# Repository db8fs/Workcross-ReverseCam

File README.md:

Workcross-ReverseCam
====================

ESP32-based pcb for providing ESD-safe power supply for a wireless Reverse Camera for an AODES Workcross UTV.

Schematics and PCB are designed using KiCad9.

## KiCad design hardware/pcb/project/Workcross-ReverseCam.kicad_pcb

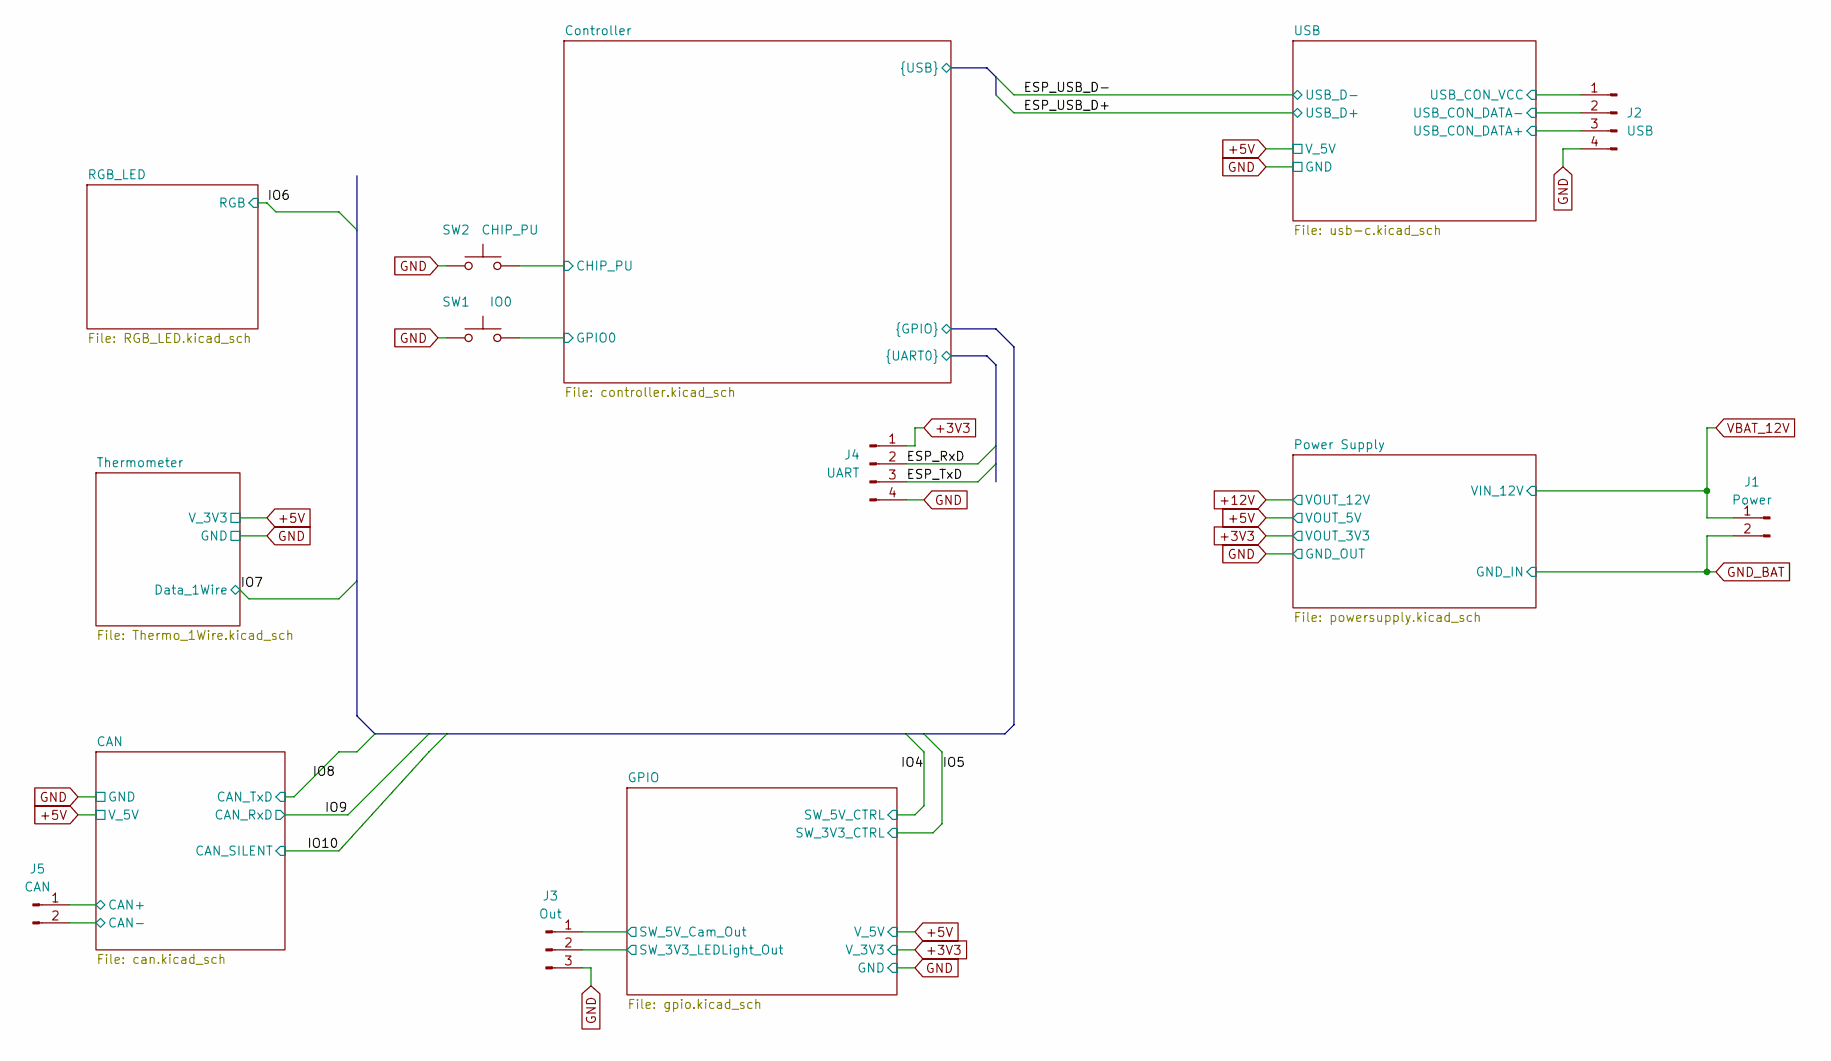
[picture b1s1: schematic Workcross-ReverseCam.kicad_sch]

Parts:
J1: Power; Molex_KK-254_AE-6410-02A_1x02_P2.54mm_Vertical
J2: USB; PinSocket_1x04_P2.54mm_Vertical
J3: Out; PinHeader_1x03_P2.54mm_Horizontal
J4: UART; PinSocket_1x04_P2.54mm_Vertical
J5: CAN; PinSocket_1x02_P2.54mm_Vertical
SW1: IO0; SW_SPST_Omron_B3FS-100xP
SW2: CHIP_PU; SW_SPST_Omron_B3FS-100xP

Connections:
+3V3: J4.1; also elsewhere on the board
/CAN/CAN+: J5.1; also elsewhere on the board
/CAN/CAN-: J5.2; also elsewhere on the board
/Controller/CHIP_PU: SW2.2; also elsewhere on the board
/Controller/ESP.ESP_RxD: J4.2; also elsewhere on the board
/Controller/ESP.ESP_TxD: J4.3; also elsewhere on the board
/Controller/ESP.ESP_USB_D+: J2.3; also elsewhere on the board
/Controller/ESP.ESP_USB_D-: J2.2; also elsewhere on the board
/Controller/GPIO0: SW1.2; also elsewhere on the board
/GPIO/SW_3V3_LEDLight_Out: J3.2; also elsewhere on the board
/GPIO/SW_5V_Cam_Out: J3.1; also elsewhere on the board
/USB/USB_CON_VCC: J2.1; also elsewhere on the board
GND: J2.4, J3.3, J4.4, SW1.1, SW2.1; also elsewhere on the board
GND_BAT: J1.2; also elsewhere on the board
VBAT_12V: J1.1; also elsewhere on the board

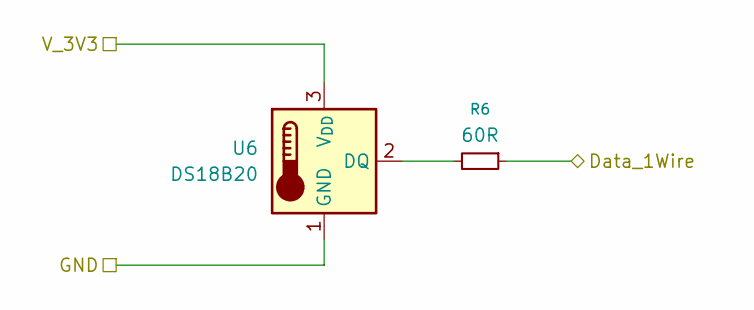
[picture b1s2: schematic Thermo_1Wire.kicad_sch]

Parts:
R6: 60R; R_1206_3216Metric_Pad1.30x1.75mm_HandSolder
U6: DS18B20; TO-92L_HandSolder

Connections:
+5V: U6.3 (V_{DD}); also elsewhere on the board
/Controller/ESP.IO7: R6.1; also elsewhere on the board
GND: U6.1 (GND); also elsewhere on the board
unnamed: R6.2, U6.2 (DQ)

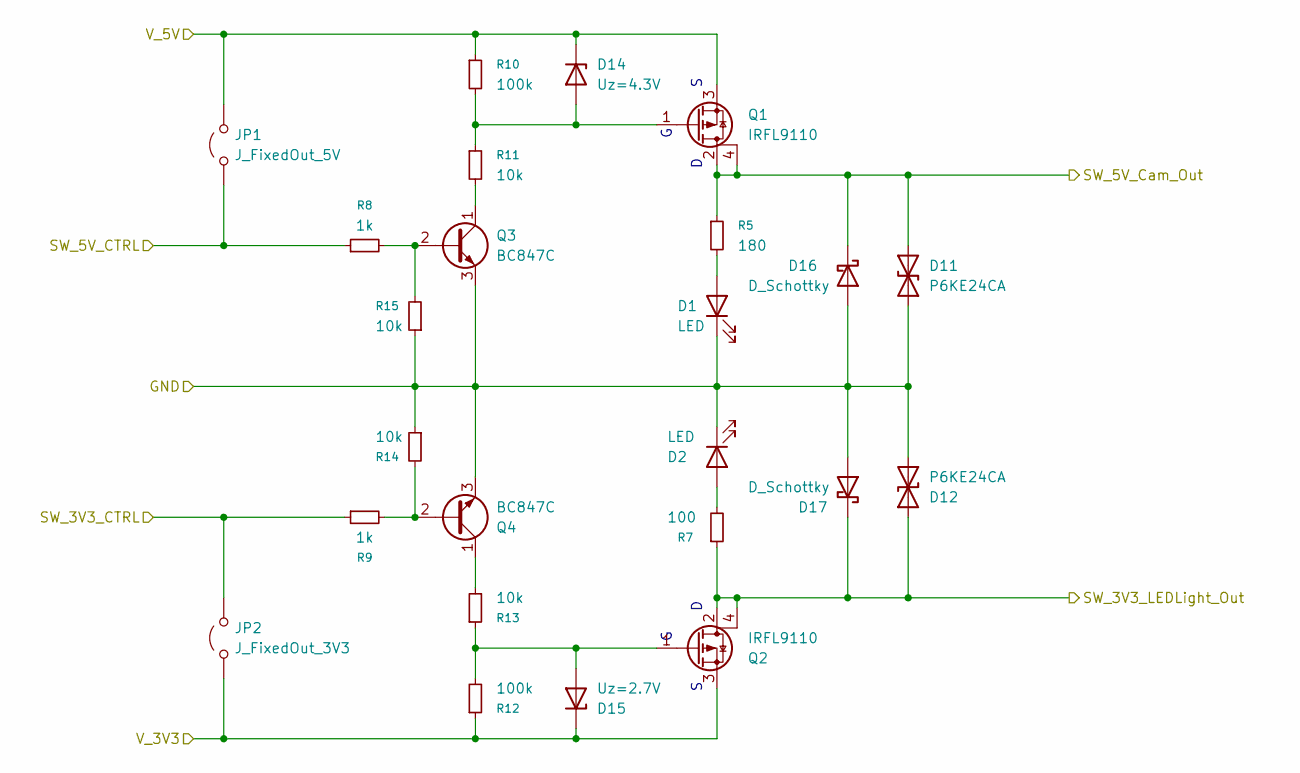
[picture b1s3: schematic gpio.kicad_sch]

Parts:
D1, D2: LED; LED_1206_3216Metric_Pad1.42x1.75mm_HandSolder
D11, D12: P6KE24CA; D_SMB_Handsoldering
D14: Uz=4.3V; D_MiniMELF_Handsoldering
D15: Uz=2.7V; D_MiniMELF_Handsoldering
D16, D17: D_Schottky
JP1: J_FixedOut_5V; TestPoint_2Pads_Pitch2.54mm_Drill0.8mm
JP2: J_FixedOut_3V3; TestPoint_2Pads_Pitch2.54mm_Drill0.8mm
Q1, Q2: IRFL9110; SOT-223-3_TabPin2
Q3, Q4: BC847C; SOT-23
R5: 180; R_1206_3216Metric_Pad1.30x1.75mm_HandSolder
R7: 100; R_1206_3216Metric_Pad1.30x1.75mm_HandSolder
R8, R9: 1k; R_1206_3216Metric_Pad1.30x1.75mm_HandSolder
R10, R12: 100k; R_1206_3216Metric_Pad1.30x1.75mm_HandSolder
R11, R13, R14, R15: 10k; R_1206_3216Metric_Pad1.30x1.75mm_HandSolder

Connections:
+3V3: D15.1 (K), JP2.1 (A), Q2.3 (S), R12.1; also elsewhere on the board
+5V: D14.1 (K), JP1.2 (B), Q1.3 (S), R10.1; also elsewhere on the board
/Controller/ESP.IO4: JP1.1 (A), R8.1; also elsewhere on the board
/Controller/ESP.IO5: JP2.2 (B), R9.1; also elsewhere on the board
/GPIO/SW_3V3_LEDLight_Out: D12.2 (A2), D17.1 (K), Q2.2 (D), Q2.4 (D), R7.1; also elsewhere on the board
/GPIO/SW_5V_Cam_Out: D11.2 (A2), D16.1 (K), Q1.2 (D), Q1.4 (D), R5.1; also elsewhere on the board
GND: D1.1 (K), D2.1 (K), D11.1 (A1), D12.1 (A1), D16.2 (A), D17.2 (A), Q3.3 (E), Q4.3 (E), R14.1, R15.1; also elsewhere on the board
unnamed: D1.2 (A), R5.2
unnamed: D2.2 (A), R7.2
unnamed: D14.2 (A), Q1.1 (G), R10.2, R11.1
unnamed: D15.2 (A), Q2.1 (G), R12.2, R13.1
unnamed: Q3.2 (B), R8.2, R15.2
unnamed: Q3.1 (C), R11.2
unnamed: Q4.2 (B), R9.2, R14.2
unnamed: Q4.1 (C), R13.2

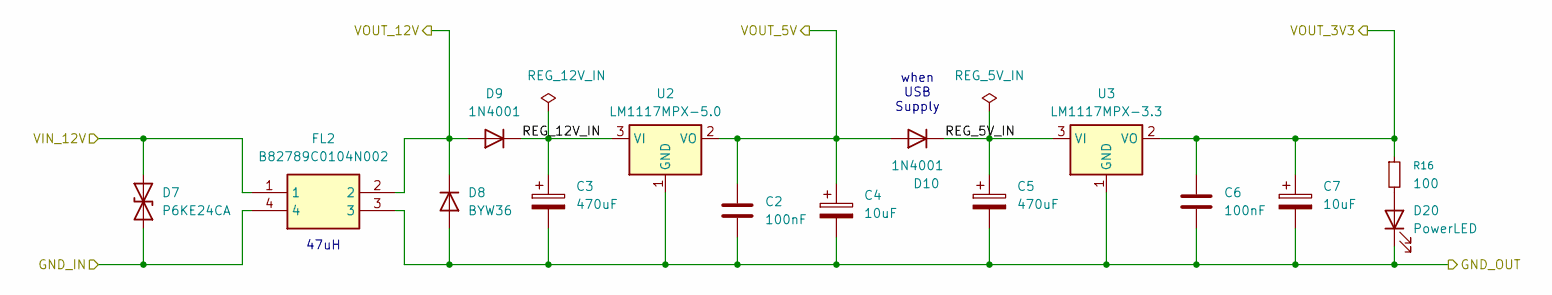
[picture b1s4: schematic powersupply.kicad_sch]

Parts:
C2, C6: 100nF; C_1206_3216Metric_Pad1.33x1.80mm_HandSolder
C3, C5: 470uF; CP_Elec_10x10
C4, C7: 10uF; CP_Elec_6.3x5.8
D7: P6KE24CA; D_SMB_Handsoldering
D8: BYW36; D_A-405_P7.62mm_Horizontal
D9, D10: 1N4001; D_DO-41_SOD81_P10.16mm_Horizontal
D20: PowerLED; LED_1206_3216Metric_Pad1.42x1.75mm_HandSolder
FL2: B82789C0104N002; B82789S0223N002; Manufacturer_Part_Number B82789S0223N002; Mouser Part Number 871-B82789S0223N002
R16: 100; R_1206_3216Metric_Pad1.30x1.75mm_HandSolder
U2: LM1117MPX-5.0; SOT-223-3_TabPin2
U3: LM1117MPX-3.3; SOT-223-3_TabPin2

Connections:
+3V3: C6.1, C7.1, R16.1, U3.2 (VO); also elsewhere on the board
+5V: C2.1, C4.1, D10.2 (A), U2.2 (VO); also elsewhere on the board
+12V: D8.1 (K), D9.2 (A), FL2.2
/Power Supply/REG_5V_IN: C5.1, D10.1 (K), U3.3 (VI)
/Power Supply/REG_12V_IN: C3.1, D9.1 (K), U2.3 (VI)
GND: C2.2, C3.2, C4.2, C5.2, C6.2, C7.2, D8.2 (A), D20.1 (K), FL2.3, U2.1 (GND), U3.1 (GND); also elsewhere on the board
GND_BAT: D7.1 (A1), FL2.4; also elsewhere on the board
unnamed: D20.2 (A), R16.2
VBAT_12V: D7.2 (A2), FL2.1; also elsewhere on the board

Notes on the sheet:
when USB Supply
47uH

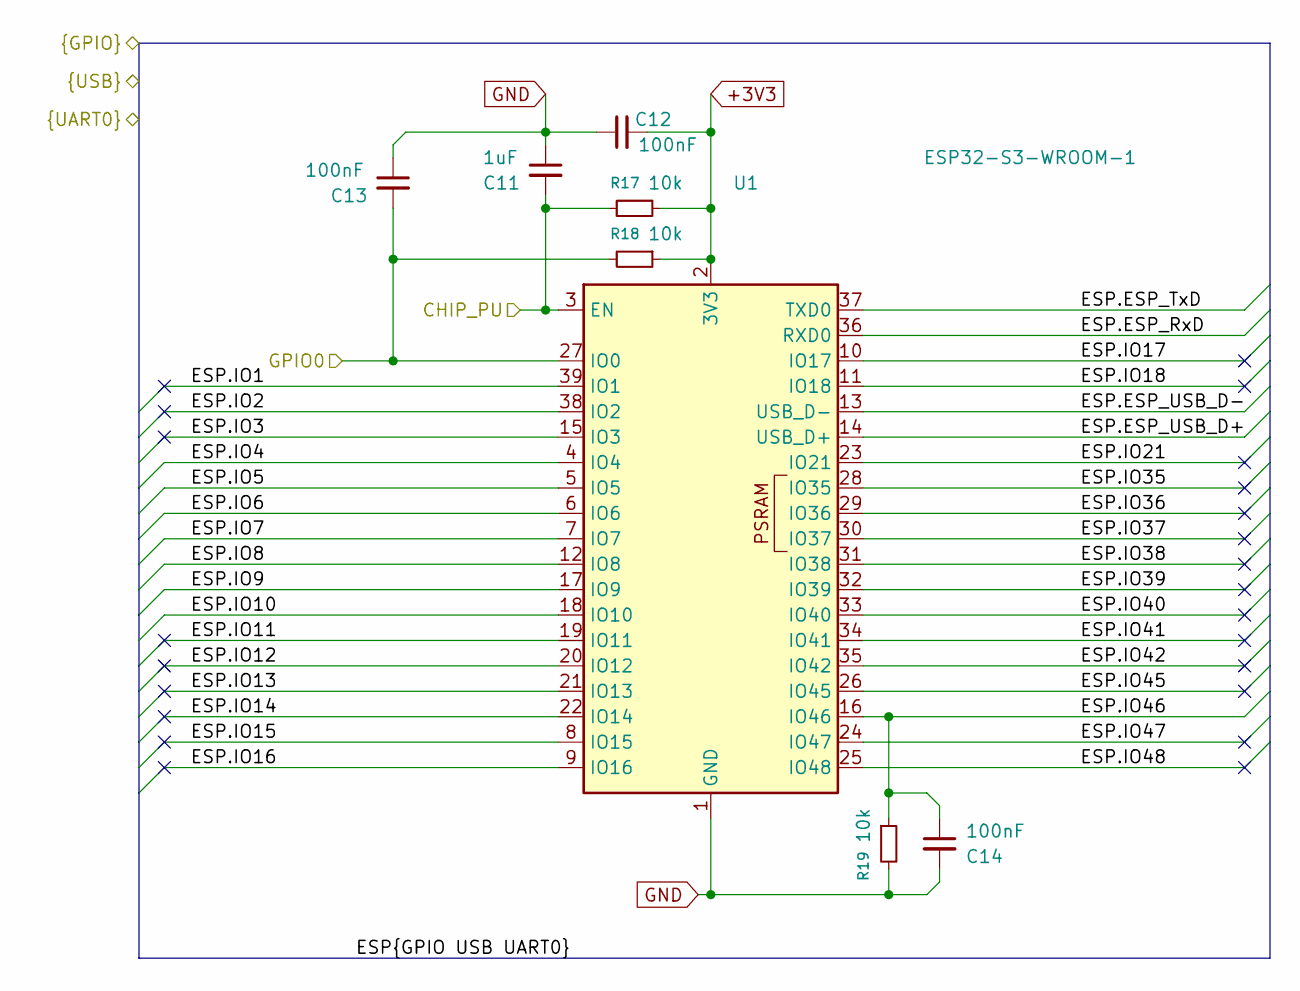
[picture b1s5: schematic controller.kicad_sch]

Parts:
C11: 1uF; C_1206_3216Metric_Pad1.33x1.80mm_HandSolder
C12, C13, C14: 100nF; C_1206_3216Metric_Pad1.33x1.80mm_HandSolder
R17, R18, R19: 10k; R_1206_3216Metric_Pad1.30x1.75mm_HandSolder
U1: ESP32-S3-WROOM-1

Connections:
+3V3: C12.2, R17.1, R18.1, U1.2 (3V3); also elsewhere on the board
/Controller/CHIP_PU: C11.2, R17.2, U1.3 (EN); also elsewhere on the board
/Controller/ESP.ESP_RxD: U1.36 (RXD0); also elsewhere on the board
/Controller/ESP.ESP_TxD: U1.37 (TXD0); also elsewhere on the board
/Controller/ESP.ESP_USB_D+: U1.14 (USB_D+); also elsewhere on the board
/Controller/ESP.ESP_USB_D-: U1.13 (USB_D-); also elsewhere on the board
/Controller/ESP.IO1: U1.39 (IO1)
/Controller/ESP.IO2: U1.38 (IO2)
/Controller/ESP.IO3: U1.15 (IO3)
/Controller/ESP.IO4: U1.4 (IO4); also elsewhere on the board
/Controller/ESP.IO5: U1.5 (IO5); also elsewhere on the board
/Controller/ESP.IO6: U1.6 (IO6); also elsewhere on the board
/Controller/ESP.IO7: U1.7 (IO7); also elsewhere on the board
/Controller/ESP.IO8: U1.12 (IO8); also elsewhere on the board
/Controller/ESP.IO9: U1.17 (IO9); also elsewhere on the board
/Controller/ESP.IO10: U1.18 (IO10); also elsewhere on the board
/Controller/ESP.IO11: U1.19 (IO11)
/Controller/ESP.IO12: U1.20 (IO12)
/Controller/ESP.IO13: U1.21 (IO13)
/Controller/ESP.IO14: U1.22 (IO14)
/Controller/ESP.IO15: U1.8 (IO15)
/Controller/ESP.IO16: U1.9 (IO16)
/Controller/ESP.IO17: U1.10 (IO17)
/Controller/ESP.IO18: U1.11 (IO18)
/Controller/ESP.IO21: U1.23 (IO21)
/Controller/ESP.IO35: U1.28 (IO35)
/Controller/ESP.IO36: U1.29 (IO36)
/Controller/ESP.IO37: U1.30 (IO37)
/Controller/ESP.IO38: U1.31 (IO38)
/Controller/ESP.IO39: U1.32 (IO39)
/Controller/ESP.IO40: U1.33 (IO40)
/Controller/ESP.IO41: U1.34 (IO41)
/Controller/ESP.IO42: U1.35 (IO42)
/Controller/ESP.IO45: U1.26 (IO45)
/Controller/ESP.IO46: C14.1, R19.1, U1.16 (IO46)
/Controller/ESP.IO47: U1.24 (IO47)
/Controller/ESP.IO48: U1.25 (IO48)
/Controller/GPIO0: C13.2, R18.2, U1.27 (IO0); also elsewhere on the board
GND: C11.1, C12.1, C13.1, C14.2, R19.2, U1.1 (GND), U1.40 (GND), U1.41 (GND); also elsewhere on the board

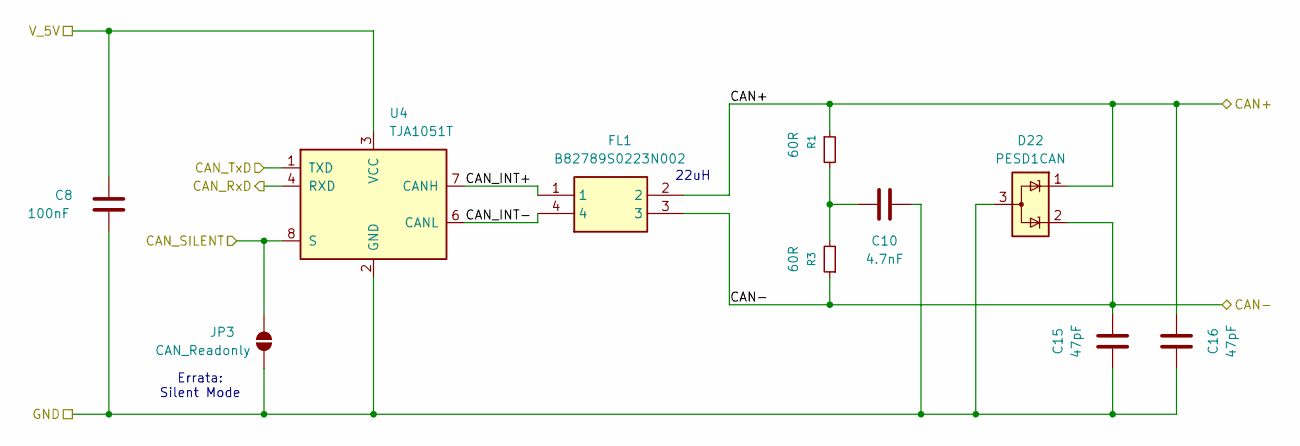
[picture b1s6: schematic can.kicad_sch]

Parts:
C8: 100nF; C_1206_3216Metric_Pad1.33x1.80mm_HandSolder
C10: 4.7nF; C_1206_3216Metric_Pad1.33x1.80mm_HandSolder
C15, C16: 47pF; C_1206_3216Metric_Pad1.33x1.80mm_HandSolder
D22: PESD1CAN; SOT-23-3
FL1: B82789S0223N002; Manufacturer_Part_Number B82789S0223N002; Mouser Part Number 871-B82789S0223N002
JP3: CAN_Readonly; SolderJumper-2_P1.3mm_Open_RoundedPad1.0x1.5mm
R1, R3: 60R; R_1206_3216Metric_Pad1.30x1.75mm_HandSolder
U4: TJA1051T; SOIC-8_3.9x4.9mm_P1.27mm

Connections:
+5V: C8.1, U4.3 (VCC); also elsewhere on the board
/CAN/CAN+: C16.1, D22.1 (K), FL1.2, R1.1; also elsewhere on the board
/CAN/CAN-: C15.1, D22.2 (K), FL1.3, R3.1; also elsewhere on the board
/CAN/CAN_INT+: FL1.1, U4.7 (CANH)
/CAN/CAN_INT-: FL1.4, U4.6 (CANL)
/Controller/ESP.IO8: U4.1 (TXD); also elsewhere on the board
/Controller/ESP.IO9: U4.4 (RXD); also elsewhere on the board
/Controller/ESP.IO10: JP3.1 (A), U4.8 (S); also elsewhere on the board
GND: C8.2, C10.1, C15.2, C16.2, D22.3 (A), JP3.2 (B), U4.2 (GND); also elsewhere on the board
unnamed: C10.2, R1.2, R3.2

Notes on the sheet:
22uH
Errata: Silent Mode

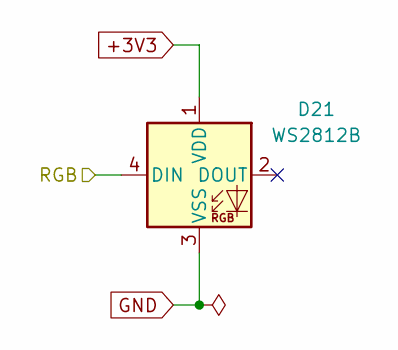
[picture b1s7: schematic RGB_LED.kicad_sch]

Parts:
D21: WS2812B; LED_WS2812B_PLCC4_5.0x5.0mm_P3.2mm

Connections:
+3V3: D21.1 (VDD); also elsewhere on the board
/Controller/ESP.IO6: D21.4 (DIN); also elsewhere on the board
GND: D21.3 (VSS); also elsewhere on the board

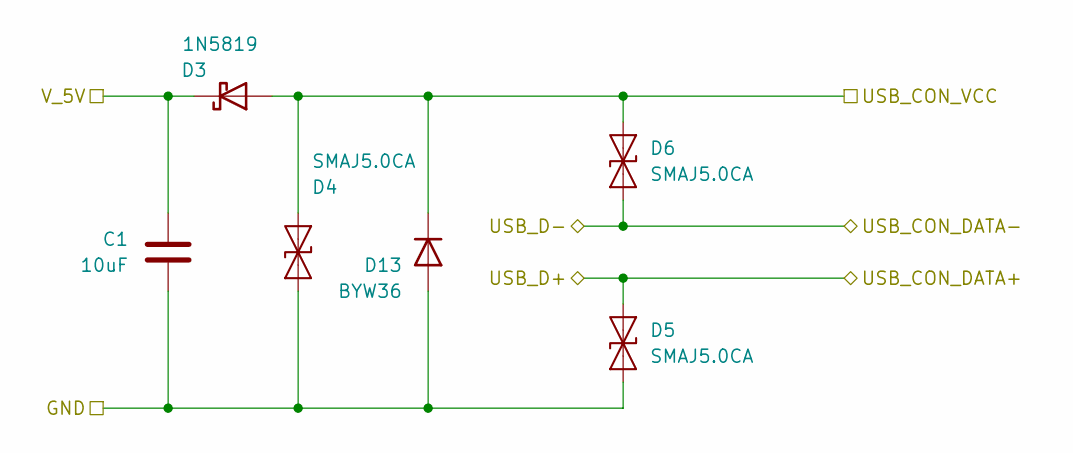
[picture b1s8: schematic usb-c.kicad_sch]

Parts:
C1: 10uF; C_1206_3216Metric_Pad1.33x1.80mm_HandSolder
D3: 1N5819; D_SOD-323
D4, D5, D6: SMAJ5.0CA; D_SMB_Handsoldering
D13: BYW36; D_A-405_P7.62mm_Horizontal

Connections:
+5V: C1.2, D3.1 (K); also elsewhere on the board
/Controller/ESP.ESP_USB_D+: D5.1 (A1); also elsewhere on the board
/Controller/ESP.ESP_USB_D-: D6.2 (A2); also elsewhere on the board
/USB/USB_CON_VCC: D3.2 (A), D4.1 (A1), D6.1 (A1), D13.1 (K); also elsewhere on the board
GND: C1.1, D4.2 (A2), D5.2 (A2), D13.2 (A); also elsewhere on the board

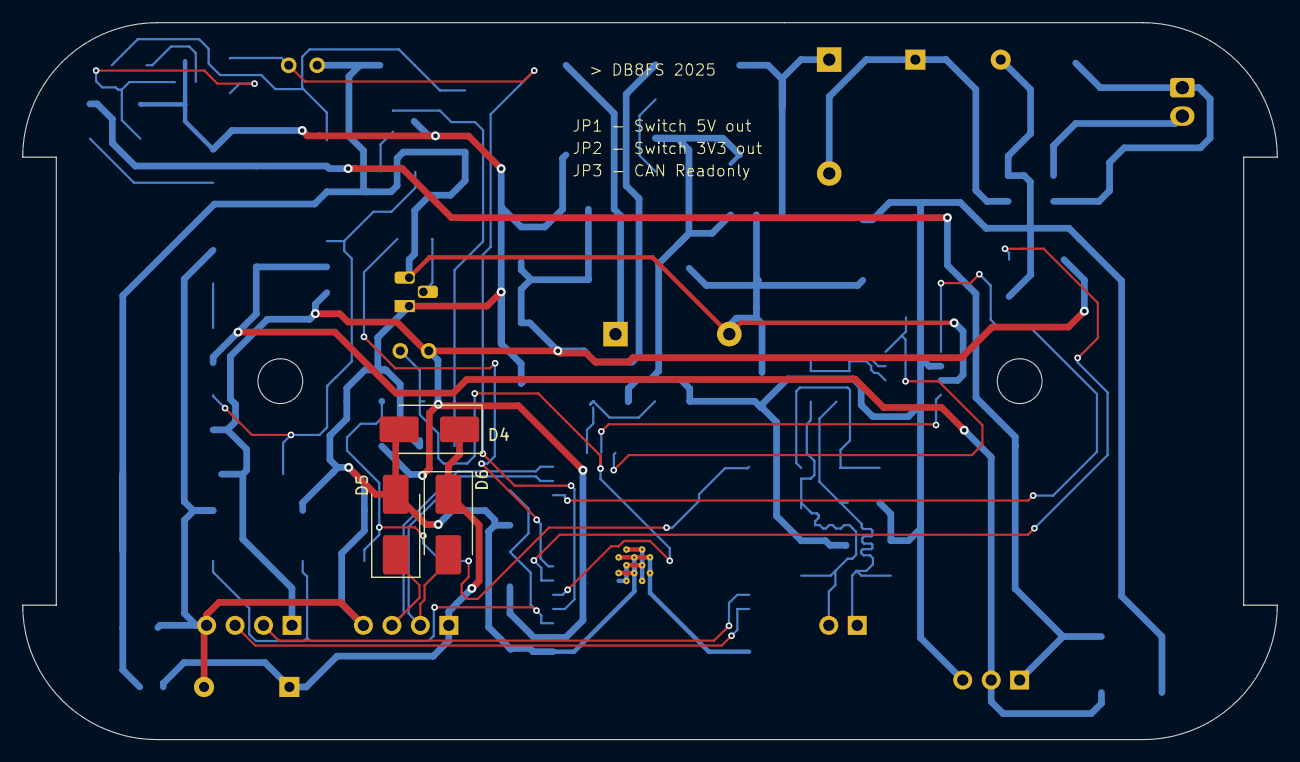
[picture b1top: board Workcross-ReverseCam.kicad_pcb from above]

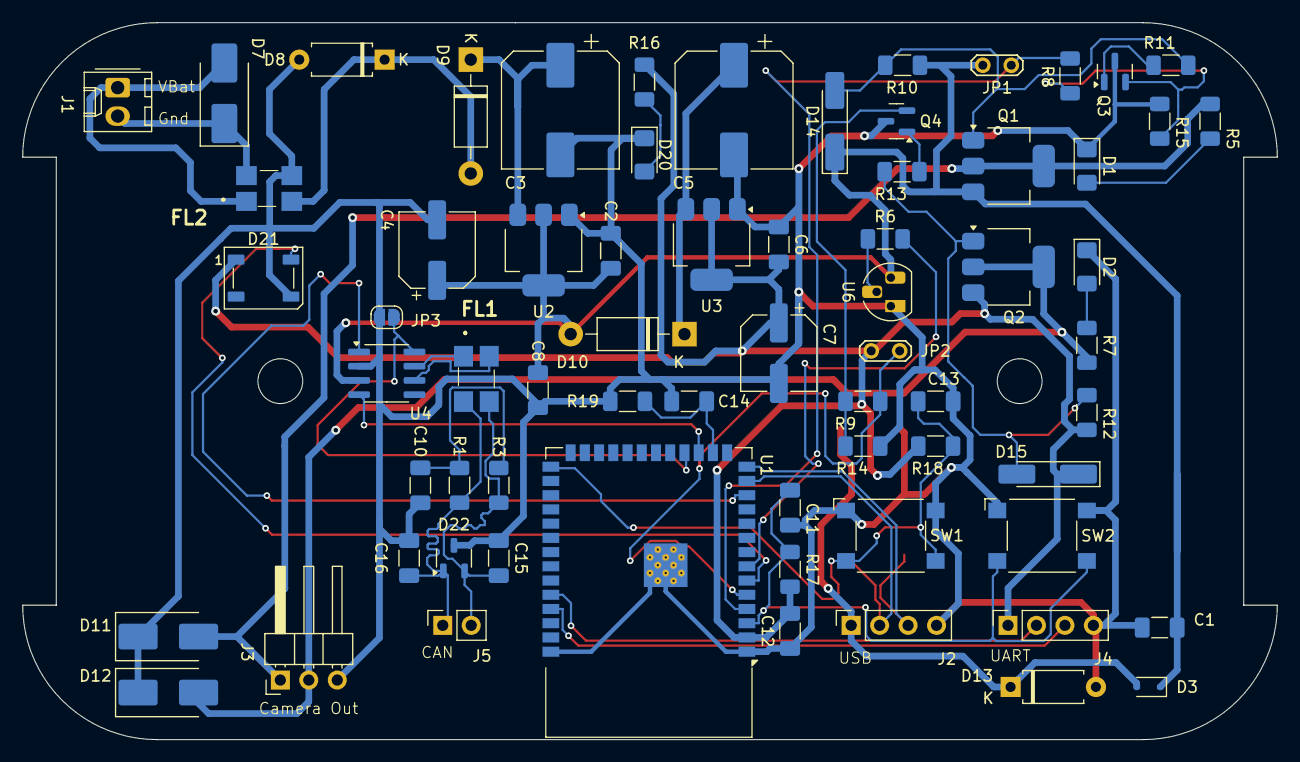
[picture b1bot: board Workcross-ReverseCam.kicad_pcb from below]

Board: 2 copper layers, 112.0 x 64.0 mm, 71 parts (68 on the bottom side), 40 nets.

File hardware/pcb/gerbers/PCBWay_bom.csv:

Designator,Quantity,Value,Footprint,Package,MPN,DNP,Mount_Type,Description,Sim.Pins,Sim.Device,Height,Manufacturer_Name,Mouser Part Number,Mouser Price/Stock,Arrow Part Number,Arrow Price/Stock
C1,1,10uF,C_1206_3216Metric_Pad1.33x1.80mm_HandSolder,,,,smt,Unpolarized capacitor,,,,,,,,
C10,1,4.7nF,C_1206_3216Metric_Pad1.33x1.80mm_HandSolder,,,,smt,Unpolarized capacitor,,,,,,,,
C11,1,1uF,C_1206_3216Metric_Pad1.33x1.80mm_HandSolder,,,,smt,"Unpolarized capacitor, small symbol",,,,,,,,
"C12, C13, C14, C2, C6, C8",6,100nF,C_1206_3216Metric_Pad1.33x1.80mm_HandSolder,,,,smt,"[C12,C13,C14]Unpolarized capacitor, small symbol; [C2,C6,C8]Unpolarized capacitor",,,,,,,,
"C15, C16",2,47pF,C_1206_3216Metric_Pad1.33x1.80mm_HandSolder,,,,smt,Unpolarized capacitor,,,,,,,,
"C3, C5",2,470uF,CP_Elec_10x10,,,,smt,Polarized capacitor,,,,,,,,
"C4, C7",2,10uF,CP_Elec_6.3x5.8,,,,smt,Polarized capacitor,,,,,,,,
"D1, D2",2,LED,LED_1206_3216Metric_Pad1.42x1.75mm_HandSolder,,,,smt,Light emitting diode,1=K 2=A,,,,,,,
"D10, D9",2,1N4001,D_DO-41_SOD81_P10.16mm_Horizontal,,,,tht,"50V 1A General Purpose Rectifier Diode, DO-41",1=K 2=A,D,,,,,,
"D11, D12, D7",3,P6KE24CA,D_SMB_Handsoldering,,,,smt,,,,,,,,,
"D13, D8",2,BYW95A,D_A-405_P7.62mm_Horizontal,,,,tht,,1=K 2=A,D,,,,,,
D14,1,Uz=4.3V,D_MiniMELF_Handsoldering,,,,smt,Zener diode,,,,,,,,
D15,1,Uz=2.7V,D_MiniMELF_Handsoldering,,,,smt,Zener diode,,,,,,,,
D20,1,PowerLED,LED_1206_3216Metric_Pad1.42x1.75mm_HandSolder,,,,smt,Light emitting diode,1=K 2=A,,,,,,,
D21,1,WS2812B,LED_WS2812B_PLCC4_5.0x5.0mm_P3.2mm,,,,smt,RGB LED with integrated controller,,,,,,,,
D22,1,PESD1CAN,SOT-23-3,,,,smt,"TVS Diode Array, 5.5V Standoff, 2 Channels, SOT23",,,,,,,,
D3,1,1N5819,D_SOD-323,,,,smt,"40V 600mV@1A 1A SOD-323 Schottky Barrier Diodes, SOD-323",,,,,,,,
"D4, D5, D6",3,SMAJ5.0CA,D_SMB_Handsoldering,,,,smt,"400W bidirectional Transient Voltage Suppressor, 5.0Vr, SMA(DO-214AC)",,,,,,,,
FL1,1,B82789S0223N002,B82789S0223N002,,B82789S0223N002,,smt,"Common Mode Filters / Chokes, |Z|=1200? at 10MHz, L x W x T :",,,3,TDK,871-B82789S0223N002,https://www.mouser.co.uk/ProductDetail/EPCOS-TDK/B82789S0223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,B82789S0223N002,https://www.arrow.com/en/products/b82789s0223n002/tdk?region=nac
FL2,1,B82789C0104N002,B82789S0223N002,,B82789S0223N002,,smt,"Common Mode Filters / Chokes, |Z|=1200? at 10MHz, L x W x T :",,,3,TDK,871-B82789S0223N002,https://www.mouser.co.uk/ProductDetail/EPCOS-TDK/B82789S0223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,B82789S0223N002,https://www.arrow.com/en/products/b82789s0223n002/tdk?region=nac
J1,1,Power,Molex_KK-254_AE-6410-02A_1x02_P2.54mm_Vertical,,,,tht,"Generic connector, single row, 01x02, script generated",,,,,,,,
J2,1,USB,PinSocket_1x04_P2.54mm_Vertical,,,,tht,"Generic connector, single row, 01x04, script generated",,,,,,,,
J3,1,Out,PinHeader_1x03_P2.54mm_Horizontal,,,,tht,"Generic connector, single row, 01x03, script generated",,,,,,,,
J4,1,UART,PinSocket_1x04_P2.54mm_Vertical,,,,tht,"Generic connector, single row, 01x04, script generated",,,,,,,,
J5,1,CAN,PinSocket_1x02_P2.54mm_Vertical,,,,tht,"Generic connector, single row, 01x02, script generated",,,,,,,,
JP1,1,J_FixedOut_5V,TestPoint_2Pads_Pitch2.54mm_Drill0.8mm,,,,tht,"Jumper, 2-pole, open",,,,,,,,
JP2,1,J_FixedOut_3V3,TestPoint_2Pads_Pitch2.54mm_Drill0.8mm,,,,tht,"Jumper, 2-pole, open",,,,,,,,
"Q1, Q2",2,IRFL9110,SOT-223-3_TabPin2,,,,smt,"P-MOSFET transistor, gate/drain/source, drain connected to mounting plane",,,,,,,,
"Q3, Q4",2,BC847C,SOT-23,,,,smt,"0.1A Ic, 45V Vce, Small Signal NPN Transistor, TO-92",,,,,,,,
"R1, R3, R6",3,60R,R_1206_3216Metric_Pad1.30x1.75mm_HandSolder,,,,smt,"Resistor, small symbol",,,,,,,,
"R10, R12",2,100k,R_1206_3216Metric_Pad1.30x1.75mm_HandSolder,,,,smt,"Resistor, small symbol",,,,,,,,
"R11, R13, R14, R15, R17, R18, R19",7,10k,R_1206_3216Metric_Pad1.30x1.75mm_HandSolder,,,,smt,"Resistor, small symbol",,,,,,,,
"R16, R7",2,100,R_1206_3216Metric_Pad1.30x1.75mm_HandSolder,,,,smt,"Resistor, small symbol",,,,,,,,
R5,1,180,R_1206_3216Metric_Pad1.30x1.75mm_HandSolder,,,,smt,"Resistor, small symbol",,,,,,,,
"R8, R9",2,1k,R_1206_3216Metric_Pad1.30x1.75mm_HandSolder,,,,smt,"Resistor, small symbol",,,,,,,,
SW1,1,IO0,SW_SPST_Omron_B3FS-100xP,,,,smt,Omron B3FS 6x6mm single pole normally-open tactile switch,,,,,,,,
SW2,1,CHIP_PU,SW_SPST_Omron_B3FS-100xP,,,,smt,Omron B3FS 6x6mm single pole normally-open tactile switch,,,,,,,,
U1,1,ESP32-S3-WROOM-1,ESP32-S3-WROOM-1,,,,smt,"RF Module, ESP32-S3 SoC, Wi-Fi 802.11b/g/n, Bluetooth, BLE, 32-bit, 3.3V, onboard antenna, SMD",,,,,,,,
U2,1,LM1117MPX-5.0,SOT-223-3_TabPin2,,,,smt,"800mA Low-Dropout Linear Regulator, 5.0V fixed output, SOT-223",,,,,,,,
U3,1,LM1117MPX-3.3,SOT-223-3_TabPin2,,,,smt,"800mA Low-Dropout Linear Regulator, 3.3V fixed output, SOT-223",,,,,,,,
U4,1,TJA1051T,SOIC-8_3.9x4.9mm_P1.27mm,,,,smt,"High-Speed CAN Transceiver, silent mode, SOIC-8",,,,,,,,
U6,1,DS18B20,TO-92L_HandSolder,,,,tht,Programmable Resolution 1-Wire Digital Thermometer TO-92,,,,,,,,

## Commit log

2025-05-24 Initial draft
